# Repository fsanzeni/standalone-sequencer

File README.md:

# Standalone Super Sixteen Sequencer

This repository contains a hardware project built in KiCad—a reimagined and streamlined version of the [Super Sixteen project](https://github.com/matthewcieplak/super-sixteen). The goal is to create a standalone sequencer suitable for Eurorack and other synthesizer setups.

## Project Overview

The original Super Sixteen design has been reworked into a modular, three-board system:
- **7 Segment Display Board:** Manages visual output.
- **DAC and Mono Jack Board:** Provides digital-to-analog conversion and audio interfacing.
- **16-Step Keyboard Board:** Features 16 Cherry MX switches paired with reverse-mount RGB LEDs for step sequencing.

> All pins are broken out for flexible connectivity. The boards are designed to work together or independently based on your setup.

## Key Modifications

- **Simplified Design:** Removed the IO expander from the original Super Sixteen to reduce complexity.
- **Modular Approach:** Each board can function as part of a larger system or as a standalone unit.
- **Fabrication Update:** The PCBs are currently in fabrication. This project is a work in progress (WIP).

## Getting Started

1. **Hardware Designs:** Navigate to the appropriate subfolder in the `hardware` directory to access the KiCad schematic and PCB layout files. There are four subfolders in here: three correspond to the three PCBs (i.e., the "keyboard", the DAC and IO board, the 3-digit 7-segment display driver). The fourth folder contains the keyboard layout files I generated with the [Keyboard Layout Editor](https://www.keyboard-layout-editor.com/), which I imported into Kicad with the excellent [kicad-kbplacer](https://github.com/adamws/kicad-kbplacer) plugin. You can use the JSON file provided in this folder to variate the switches' layout without having to go through the hassle of moving things around precisely on Kicad :).
2. **Software Development:** The `software` folder is currently empty. Firmware or control software will be added as the project develops.
3. **Documentation:** Detailed build instructions, assembly guides, and design notes will be provided in the `documentation` folder over time.

## Hardware Design
As mentioned above, ths repo contains three PCBs:

_The keyboard PCB, with 16 steps and seven function buttons, all using Cherry MX keyswitches_

_The DAC, opamp and IO board. I am using DIP packages for the two main ICs just because I had them laying around. The conversion to SMD packages is trivial - and there's plenty of space on the board!_

_The 7 segment driver pcb. I'm using a three-digit unit, 0.56" tall. Everything is driven by a 74HC595 to reduce the pins needed for interfacing with a microcontroller._

You will notice the glaring omission of a microcontroller from this setup. I am using the venerable Arduino MEGA as the brains of the operation, so that I have enough pins not to worry about faffing around with multiplexers and the like. 

## Inspiration

This project draws inspiration from the original [Super Sixteen project](https://github.com/matthewcieplak/super-sixteen). Visit their repository to learn more about the design and evolution of the sequencer.

## License

Code: GPL3.0 Hardware: cc-by-sa-3.0

## Contributing

Contributions, issues, and feature requests are welcome. Please feel free to open an issue or submit a pull request.

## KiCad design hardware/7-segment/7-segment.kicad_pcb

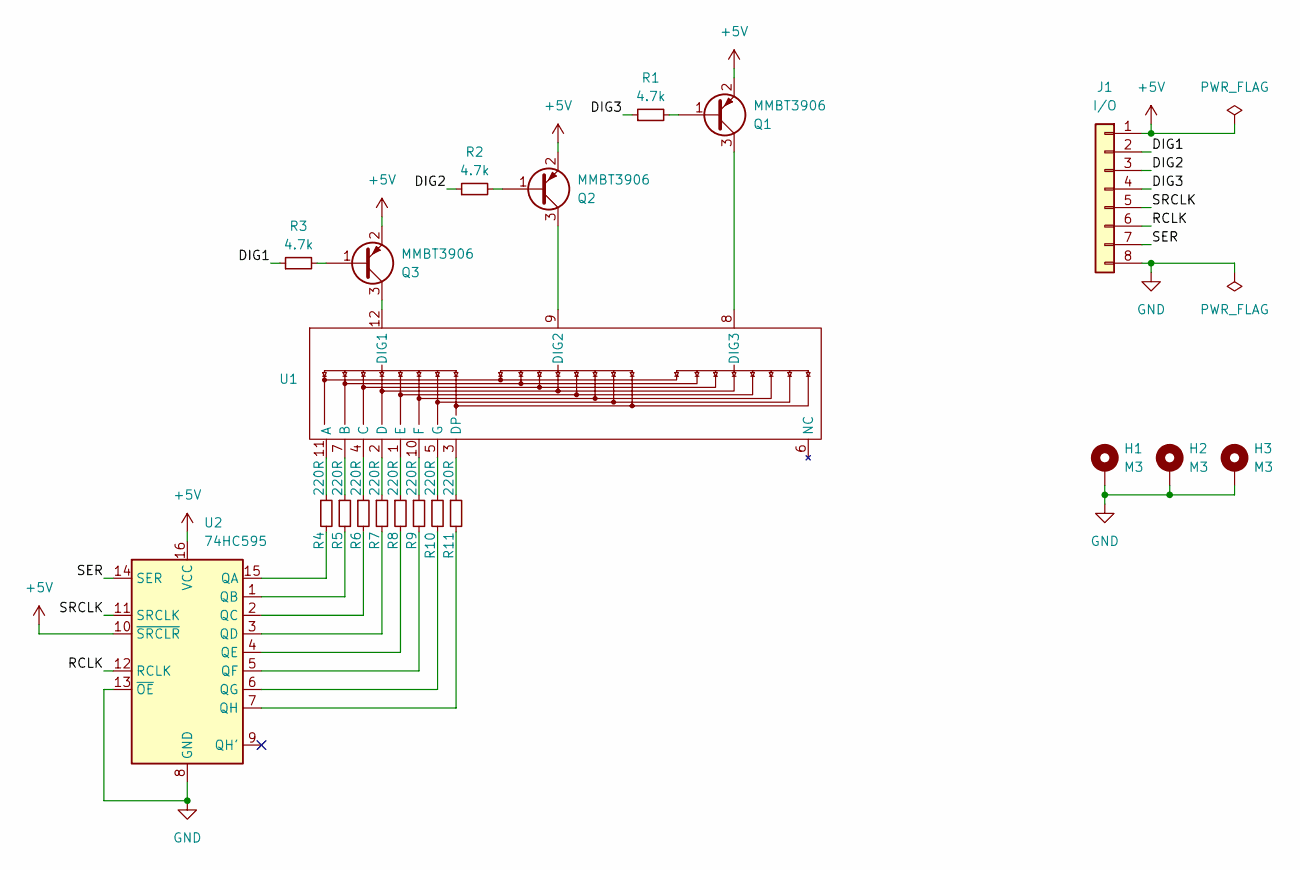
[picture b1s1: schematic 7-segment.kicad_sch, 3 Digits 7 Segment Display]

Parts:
H1, H2, H3: M3; MountingHole_3.2mm_M3_DIN965_Pad
J1: I/O; PinHeader_1x08_P2.54mm_Vertical
Q1, Q2, Q3: MMBT3906; SOT-23
R1, R2, R3: 4.7k; R_0603_1608Metric_Pad0.98x0.95mm_HandSolder
R4, R5, R6, R7, R8, R9, R10, R11: 220R; R_0603_1608Metric_Pad0.98x0.95mm_HandSolder
U1: FJ5361BH
U2: 74HC595; SOP-16_3.9x9.9mm_P1.27mm

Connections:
+5V: J1.1, Q1.2 (E), Q2.2 (E), Q3.2 (E), U2.10 (~SRCLR), U2.16 (VCC)
/DIG1: J1.2, R3.1
/DIG2: J1.3, R2.1
/DIG3: J1.4, R1.1
/RCLK: J1.6, U2.12 (RCLK)
/SER: J1.7, U2.14 (SER)
/SRCLK: J1.5, U2.11 (SRCLK)
GND: H1.1, H2.1, H3.1, J1.8, U2.8 (GND), U2.13 (~OE)
unnamed: Q1.1 (B), R1.2
unnamed: Q1.3 (C), U1.8 (DIG3)
unnamed: Q2.1 (B), R2.2
unnamed: Q2.3 (C), U1.9 (DIG2)
unnamed: Q3.1 (B), R3.2
unnamed: Q3.3 (C), U1.12 (DIG1)
unnamed: R4.1, U1.11 (A)
unnamed: R5.1, U1.7 (B)
unnamed: R6.1, U1.4 (C)
unnamed: R7.1, U1.2 (D)
unnamed: R11.1, U1.3 (DP)
unnamed: R8.1, U1.1 (E)
unnamed: R9.1, U1.10 (F)
unnamed: R10.1, U1.5 (G)
unnamed: R4.2, U2.15 (QA)
unnamed: R5.2, U2.1 (QB)
unnamed: R6.2, U2.2 (QC)
unnamed: R7.2, U2.3 (QD)
unnamed: R8.2, U2.4 (QE)
unnamed: R9.2, U2.5 (QF)
unnamed: R10.2, U2.6 (QG)
unnamed: R11.2, U2.7 (QH)

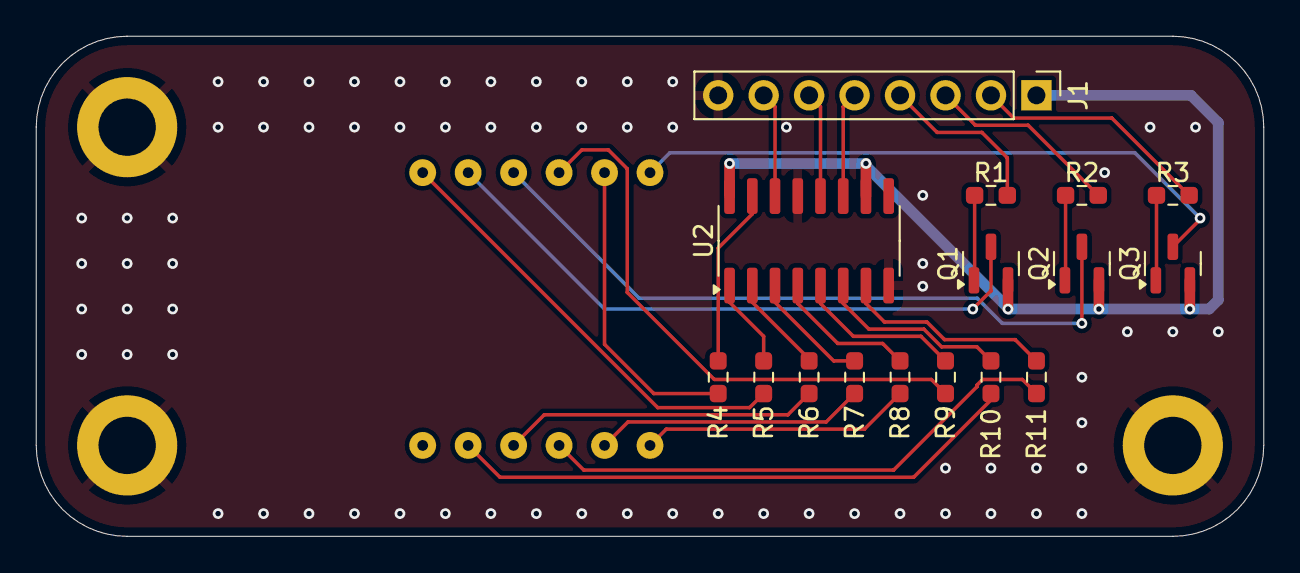
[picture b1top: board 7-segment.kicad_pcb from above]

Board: 2 copper layers, 68.6 x 27.9 mm, 20 parts (1 on the bottom side), 30 nets.

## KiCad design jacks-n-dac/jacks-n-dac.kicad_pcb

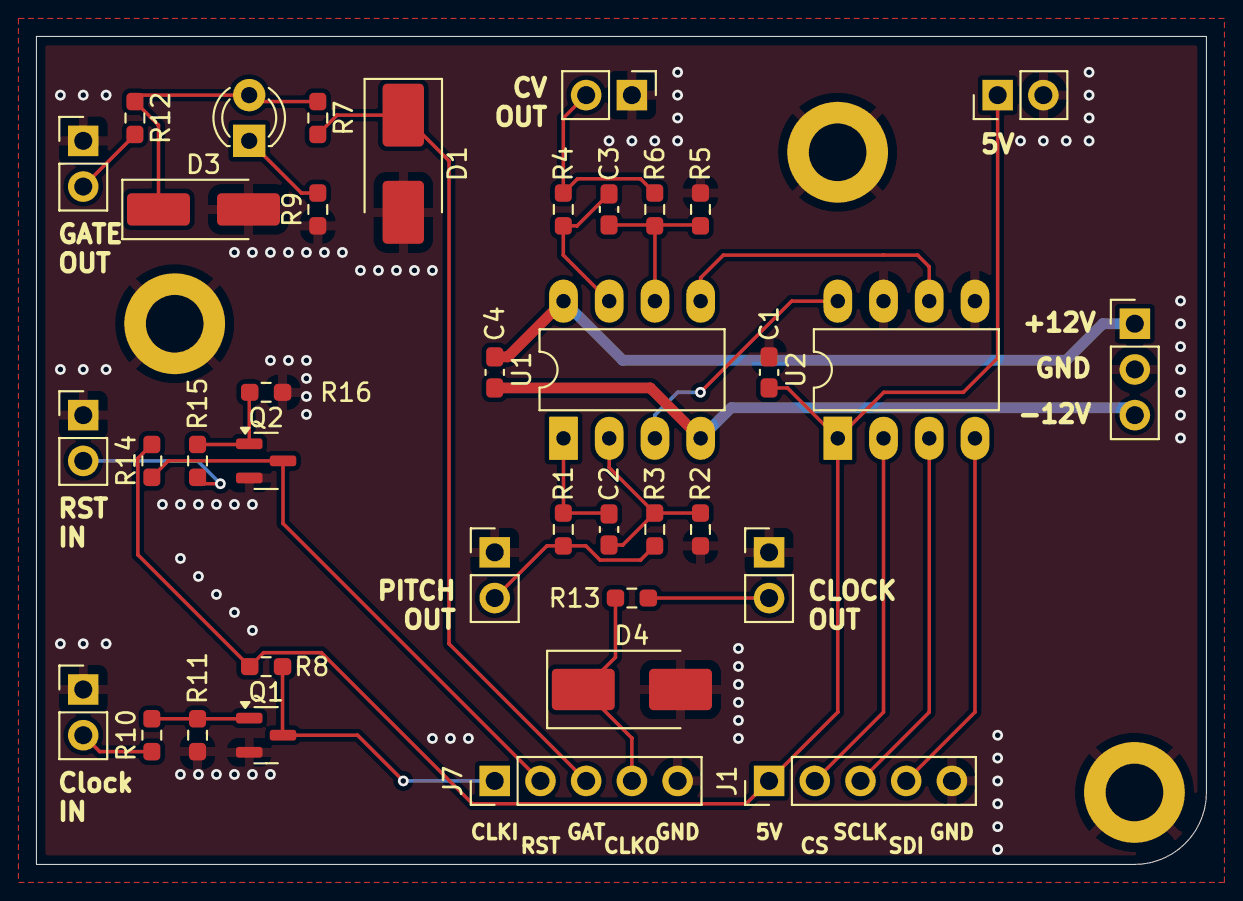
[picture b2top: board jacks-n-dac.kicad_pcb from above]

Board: 2 copper layers, 65.0 x 46.0 mm, 41 parts (0 on the bottom side), 27 nets.

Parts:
C1, C4: 100nF; C_0603_1608Metric_Pad1.08x0.95mm_HandSolder
C2, C3: 22pF; C_0603_1608Metric_Pad1.08x0.95mm_HandSolder
D1, D4: 1SMB5918BT3G; D_SMB_Handsoldering
D2: GATE; LED_D3.0mm_FlatTop
D3: SS34F; D_SMA_Handsoldering
H1, H2, H3: M3; MountingHole_3.2mm_M3_DIN965_Pad
J1: DAC; PinHeader_1x05_P2.54mm_Vertical
J2: 12V IN; PinHeader_1x03_P2.54mm_Vertical
J3: 5V IN; PinHeader_1x02_P2.54mm_Vertical
J4: GateOut; PinHeader_1x02_P2.54mm_Vertical
J5: ClockIn; PinHeader_1x02_P2.54mm_Vertical
J6: ClockOut; PinHeader_1x02_P2.54mm_Vertical
J7: INPUTS; PinHeader_1x05_P2.54mm_Vertical
J8: PitchOut; PinHeader_1x02_P2.54mm_Vertical
J9: CVOut; PinHeader_1x02_P2.54mm_Vertical
J10: ResetIn; PinHeader_1x02_P2.54mm_Vertical
Q1, Q2: MMBT3904; SOT-23
R1, R4, R7, R9, R12, R13: 1k; R_0603_1608Metric_Pad0.98x0.95mm_HandSolder
R2, R3, R5, R6, R8, R14: 10k; R_0603_1608Metric_Pad0.98x0.95mm_HandSolder
R10, R15: 100k; R_0603_1608Metric_Pad0.98x0.95mm_HandSolder
R11, R16: 1M; R_0603_1608Metric_Pad0.98x0.95mm_HandSolder
U1: TL072; DIP-8_W7.62mm_LongPads
U2: MCP4822; DIP-8_W7.62mm_LongPads

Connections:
+5V: C1.2, J1.1, J3.1, R8.2, R14.2, U2.1 (Vdd)
+12V: C4.2, J2.1, U1.8 (V+)
-12V: C4.1, J2.3, U1.4 (V-)
/CLKIN: J7.1, Q1.3 (C), R8.1
/CLKOUT: D4.1 (K), J7.4, R13.2
/CS_DAC: J1.2, U2.2 (~CS)
/CV: J9.2, R4.2, R6.2
/GATE: D1.1 (K), J7.3, R7.2
/MOSI: J1.4, U2.4 (SDI)
/PITCH: J8.2, R1.2, R3.2
/RSTIN: J7.2, Q2.3 (C), R14.1
/SCLK: J1.3, U2.3 (SCK)
GND: C1.1, D1.2 (A), D3.2 (A), D4.2 (A), H1.1, H2.1, H3.1, J1.5, J2.2, J3.2, J4.1, J5.1, J6.1, J7.5, J8.1, J9.1, J10.1, Q1.2 (E), Q2.2 (E), R2.1, R5.1, R9.1, R11.1, R16.1, U2.5 (~LDAC), U2.7 (Vss)
unnamed: C2.2, R1.1, U1.1
unnamed: C3.2, R4.1, U1.7
unnamed: D2.2 (A), D3.1 (K), R7.1, R12.1
unnamed: D2.1 (K), R9.2
unnamed: J4.2, R12.2
unnamed: J5.2, R10.1
unnamed: J6.2, R13.1
unnamed: J10.2, R15.1
unnamed: Q1.1 (B), R10.2, R11.2
unnamed: Q2.1 (B), R15.2, R16.2
unnamed: U1.3 (+), U2.8 (VA)
unnamed: C2.1, R2.2, R3.1, U1.2 (-)
unnamed: U1.5 (+), U2.6 (VB)
unnamed: C3.1, R5.2, R6.1, U1.6 (-)

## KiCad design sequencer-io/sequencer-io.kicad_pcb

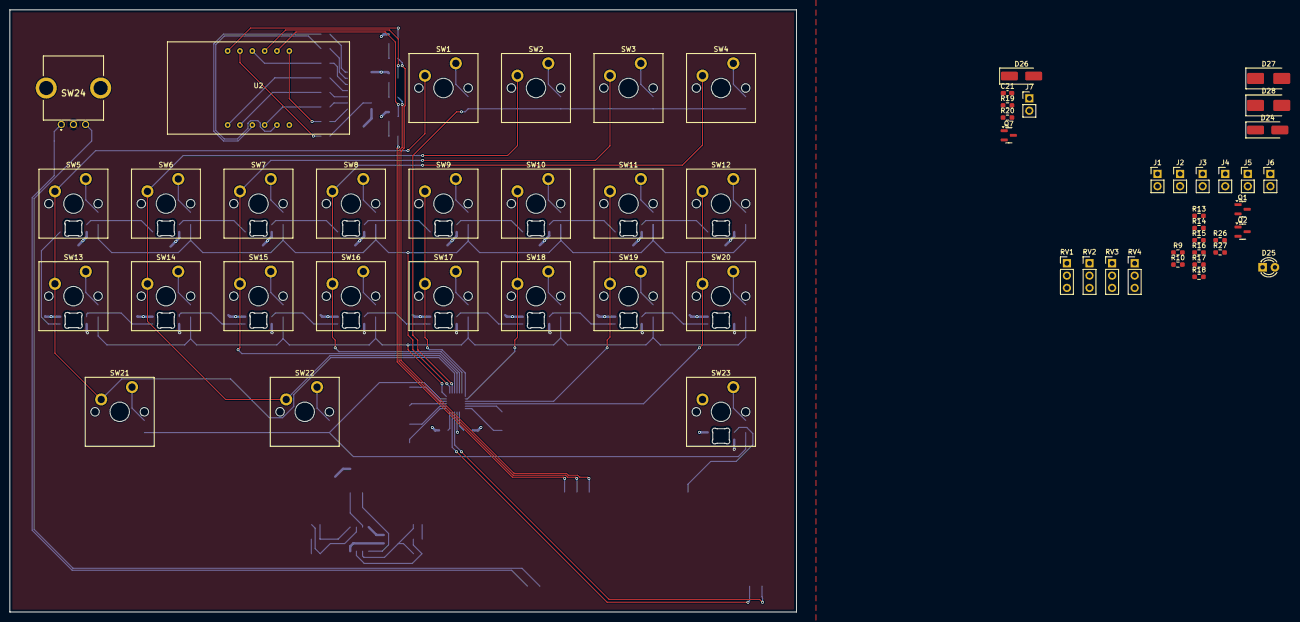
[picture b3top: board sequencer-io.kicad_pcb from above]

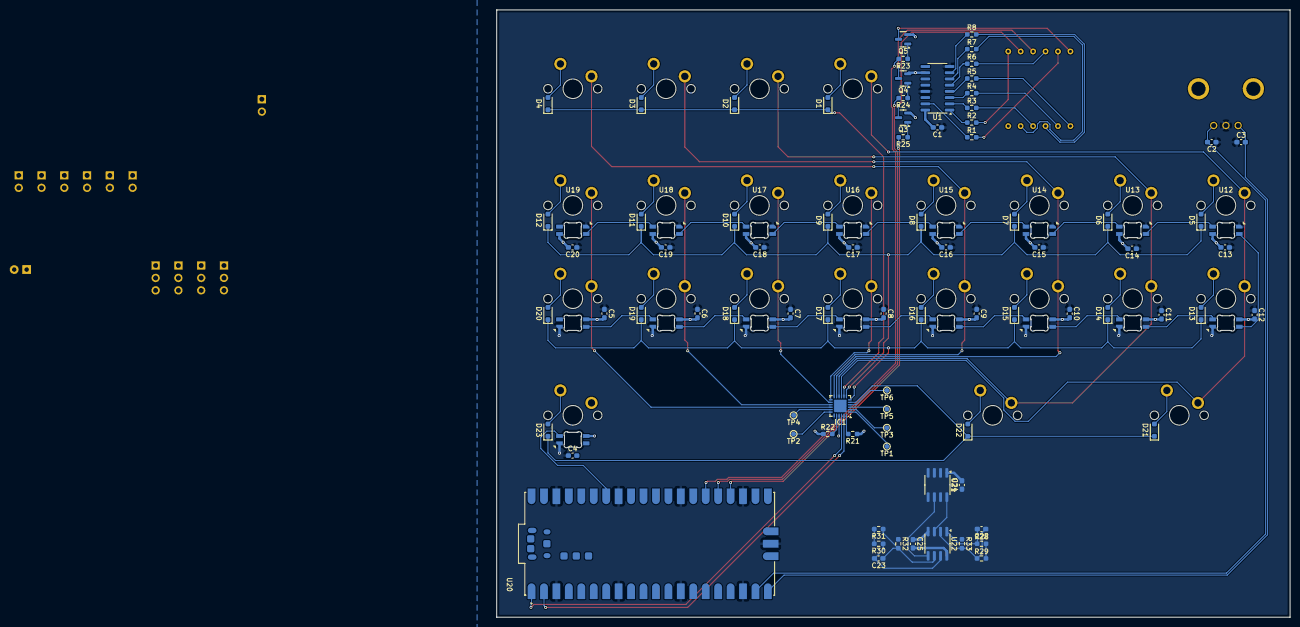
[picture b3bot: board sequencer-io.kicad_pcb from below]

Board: 4 copper layers, 162.0 x 124.0 mm, 154 parts (97 on the bottom side), 113 nets.

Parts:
C1, C2, C3, C4, C5, C6, C7, C8, C9, C10, C11, C12, C13, C14, C15, C16, C17, C18, C19, C20, C24, C25: 100nF; C_0603_1608Metric_Pad1.08x0.95mm_HandSolder
C21: 47uF; C_0603_1608Metric_Pad1.08x0.95mm_HandSolder
C22, C23: 22pF; C_0603_1608Metric_Pad1.08x0.95mm_HandSolder
D1, D2, D3, D4, D5, D6, D7, D8, D9, D10, D11, D12, D13, D14, D15, D16, D17, D18, D19, D20, D21, D22, D23: 1N4148W; D_SOD-323_HandSoldering
D24, D26: SS34F; D_SMA_Handsoldering
D25: GATE; LED_D3.0mm_FlatTop
D27, D28: 1SMB5918BT3G; D_SMB_Handsoldering
IC1: TCA8418RTWR; QFN-24-1EP_4x4mm_P0.5mm_EP2.5x2.5mm
J1: ClockIn; PinHeader_1x02_P2.54mm_Vertical
J2: GateOut; PinHeader_1x02_P2.54mm_Vertical
J3: ClockOut; PinHeader_1x02_P2.54mm_Vertical
J4: PitchOut; PinHeader_1x02_P2.54mm_Vertical
J5: CVOut; PinHeader_1x02_P2.54mm_Vertical
J6: ResetIn; PinHeader_1x02_P2.54mm_Vertical
J7: 5V EXT; PinHeader_1x02_P2.54mm_Vertical
Q1, Q2: MMBT3904; SOT-23
Q3, Q4, Q5: MMBT3906; SOT-23
Q7: DMG2305UX-7; SOT-23
R1, R2, R3, R4, R5, R6, R7, R8: 100R; R_0603_1608Metric_Pad0.98x0.95mm_HandSolder
R9, R16, R19, R20, R21, R22, R29, R31, R32, R33: 10k; R_0603_1608Metric_Pad0.98x0.95mm_HandSolder
R10, R15, R26, R27, R28, R30: 1k; R_0603_1608Metric_Pad0.98x0.95mm_HandSolder
R13, R17: 100k; R_0603_1608Metric_Pad0.98x0.95mm_HandSolder
R14, R18: 1M; R_0603_1608Metric_Pad0.98x0.95mm_HandSolder
R23, R24, R25: 680R; R_0603_1608Metric_Pad0.98x0.95mm_HandSolder
RV1: PITCH; PinHeader_1x03_P2.54mm_Vertical
RV2: OCTAVE; PinHeader_1x03_P2.54mm_Vertical
RV3: LENGTH; PinHeader_1x03_P2.54mm_Vertical
RV4: CV; PinHeader_1x03_P2.54mm_Vertical
SW1, SW2, SW3, SW4, SW5, SW6, SW7, SW8, SW9, SW10, SW11, SW12, SW13, SW14, SW15, SW16, SW17, SW18, SW19, SW20, SW23: SW_Push; SW_Cherry_MX_PCB_1.00u
SW21, SW22: SW_Push; SW_Cherry_MX_PCB_2.00u
SW24: RotaryEncoder; EC12E2430404
TP1, TP2, TP3, TP4, TP5, TP6: TestPoint_Small; TestPoint_Pad_D1.0mm
U1: 74HC595; SOIC-16_3.9x9.9mm_P1.27mm
U2: FJ5361BH
U3, U4, U5, U6, U7, U8, U9, U10, U11: SK6812MINI-E-012
U12, U13, U14, U15, U16, U17, U18, U19: SK6812MINI-E-012-ROT
U20: SC0915
U21: MCP4822; SOIC-8_3.9x4.9mm_P1.27mm
U22: TL072; SOIC-8_3.9x4.9mm_P1.27mm

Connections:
+3.3V: IC1.21 (VCC), R9.2, R16.2, R19.1, R20.1, R21.1, R22.1, RV1.1, RV2.1, RV3.1, RV4.1
+5V: C1.2, C4.2, C5.2, C6.2, C7.2, C8.2, C9.2, C10.2, C11.2, C12.2, C13.2, C14.2, C15.2, C16.2, C17.2, C18.2, C19.2, C20.2, C21.2, C24.2, D26.1 (K), Q3.2 (E), Q4.2 (E), Q5.2 (E), Q7.2 (S), U1.10 (~SRCLR), U1.16 (VCC), U3.3 (VDD), U4.3 (VDD), U5.3 (VDD), U6.3 (VDD), U7.3 (VDD), U8.3 (VDD), U9.3 (VDD), U10.3 (VDD), U11.3 (VDD), U12.3 (VDD), U13.3 (VDD), U14.3 (VDD), U15.3 (VDD), U16.3 (VDD), U17.3 (VDD), U18.3 (VDD), U19.3 (VDD), U20.39 (VSYS), U21.1 (Vdd)
+12V: C25.2, U22.8 (V+)
-12V: C25.1, U22.4 (V-)
/DAC/CV: R30.2, R31.2
/DAC/PITCH: R28.2, R29.2
/DAC/SCLK: U1.11 (SRCLK), U21.3 (SCK)
/IOs/CLKIN: Q1.3 (C), R9.1
/IOs/CLKOUT: D28.1 (K), R27.2
/IOs/DIGIT_1: R23.2, U20.26 (GP20)
/IOs/DIGIT_2: R24.2, U20.25 (GP19)
/IOs/DIGIT_3: R25.2, U20.24 (GP18)
/IOs/ENC_A: C3.2, SW24.A, U20.20 (GP15)
/IOs/ENC_B: C2.2, SW24.B, U20.19 (GP14)
/IOs/GATE: D27.1 (K), R26.2
/IOs/RSTIN: Q2.3 (C), R16.1
/LEDs/PXL: U3.2 (DIN), U20.34 (GP28)
/Switches/SCL: IC1.23 (SCL), R20.2, U20.2 (GP1)
/Switches/SDA: IC1.22 (SDA), R19.2, U20.1 (GP0)
COL0: IC1.9 (COL0), SW1.1, SW5.1, SW13.1, SW21.1
COL1: IC1.10 (COL1), SW2.1, SW6.1, SW14.1, SW22.1
COL2: IC1.11 (COL2), SW3.1, SW7.1, SW15.1, SW23.1
COL3: IC1.12 (COL3), SW4.1, SW8.1, SW16.1
COL4: IC1.13 (COL4), SW9.1, SW17.1
COL5: IC1.14 (COL5), SW10.1, SW18.1
COL6: IC1.15 (COL6), SW11.1, SW19.1
COL7: IC1.16 (COL7), SW12.1, SW20.1
GND: C1.1, C2.1, C3.1, C4.1, C5.1, C6.1, C7.1, C8.1, C9.1, C10.1, C11.1, C12.1, C13.1, C14.1, C15.1, C16.1, C17.1, C18.1, C19.1, C20.1, C21.1, C24.1, D24.2 (A), D27.2 (A), D28.2 (A), IC1.19 (GND), IC1.25 (EP), J7.2, Q1.2 (E), Q2.2 (E), R10.1, R14.1, R18.1, R32.1, R33.1, RV4.3, SW24.C, U1.8 (GND), U1.13 (~OE), U3.1 (GND), U4.1 (GND), U5.1 (GND), U6.1 (GND), U7.1 (GND), U8.1 (GND), U9.1 (GND), U10.1 (GND), U11.1 (GND), U12.1 (GND), U13.1 (GND), U14.1 (GND), U15.1 (GND), U16.1 (GND), U17.1 (GND), U18.1 (GND), U19.1 (GND), U20.3 (GND), U20.8 (GND), U20.13 (GND), U20.18 (GND), U20.23 (GND), U20.28 (GND), U20.33 (AGND), U20.38 (GND), U20.D2 (GND), U21.5 (~LDAC), U21.7 (Vss)
unnamed: C22.2, R28.1, U22.1
unnamed: C23.2, R30.1, U22.7
unnamed: D1.2 (A), SW1.2
unnamed: D2.2 (A), SW2.2
unnamed: D3.2 (A), SW3.2
unnamed: D4.2 (A), SW4.2
unnamed: D5.2 (A), SW5.2
unnamed: D6.2 (A), SW6.2
unnamed: D7.2 (A), SW7.2
unnamed: D8.2 (A), SW8.2
unnamed: D9.2 (A), SW9.2
unnamed: D10.2 (A), SW10.2
unnamed: D11.2 (A), SW11.2
unnamed: D12.2 (A), SW12.2
unnamed: D13.2 (A), SW13.2
unnamed: D14.2 (A), SW14.2
unnamed: D15.2 (A), SW15.2
unnamed: D16.2 (A), SW16.2
unnamed: D17.2 (A), SW17.2
unnamed: D18.2 (A), SW18.2
unnamed: D19.2 (A), SW19.2
unnamed: D20.2 (A), SW20.2
unnamed: D21.2 (A), SW21.2
unnamed: D22.2 (A), SW22.2
unnamed: D23.2 (A), SW23.2
unnamed: D24.1 (K), D25.2 (A), R15.1, R26.1
unnamed: D25.1 (K), R10.2
unnamed: D26.2 (A), Q7.1 (G), U20.40 (VBUS)
unnamed: IC1.17 (COL8), TP4.1
unnamed: IC1.18 (COL9), TP2.1
unnamed: IC1.4 (ROW4), TP6.1
unnamed: IC1.3 (ROW5), TP5.1
unnamed: IC1.2 (ROW6), TP3.1
unnamed: IC1.1 (ROW7), TP1.1
unnamed: IC1.24 (~INT), R21.2
unnamed: IC1.20 (~RESET), R22.2
unnamed: J7.1, Q7.3 (D)
unnamed: Q1.1 (B), R13.2, R14.2
unnamed: Q2.1 (B), R17.2, R18.2
unnamed: Q3.1 (B), R25.1
unnamed: Q3.3 (C), U2.8 (DIGIT_3)
unnamed: Q4.1 (B), R24.1
unnamed: Q4.3 (C), U2.9 (DIGIT_2)
unnamed: Q5.1 (B), R23.1
unnamed: Q5.3 (C), U2.12 (DIGIT_1)
unnamed: R1.1, U1.15 (QA)
unnamed: R2.1, U1.1 (QB)
unnamed: R3.1, U1.2 (QC)
unnamed: R4.1, U1.3 (QD)
unnamed: R5.1, U1.4 (QE)
unnamed: R6.1, U1.5 (QF)
unnamed: R7.1, U1.6 (QG)
unnamed: R8.1, U1.7 (QH)
unnamed: R1.2, U2.11 (A)
unnamed: R2.2, U2.7 (B)
unnamed: R3.2, U2.4 (C)
unnamed: R4.2, U2.2 (D)
unnamed: R8.2, U2.3 (DP)
unnamed: R5.2, U2.1 (E)
unnamed: R6.2, U2.10 (F)
unnamed: R7.2, U2.5 (G)
unnamed: U3.4 (DOUT), U4.2 (DIN)
unnamed: U4.4 (DOUT), U5.2 (DIN)
unnamed: U5.4 (DOUT), U6.2 (DIN)
unnamed: U6.4 (DOUT), U7.2 (DIN)
unnamed: U7.4 (DOUT), U8.2 (DIN)
unnamed: U8.4 (DOUT), U9.2 (DIN)
unnamed: U9.4 (DOUT), U10.2 (DIN)
unnamed: U10.4 (DOUT), U11.2 (DIN)
unnamed: U11.4 (DOUT), U12.2 (DIN)
unnamed: U12.4 (DOUT), U13.2 (DIN)
unnamed: U13.4 (DOUT), U14.2 (DIN)
unnamed: U14.4 (DOUT), U15.2 (DIN)
unnamed: U15.4 (DOUT), U16.2 (DIN)
unnamed: U16.4 (DOUT), U17.2 (DIN)
unnamed: U17.4 (DOUT), U18.2 (DIN)
unnamed: U18.4 (DOUT), U19.2 (DIN)
unnamed: U21.8 (VA), U22.3 (+)
unnamed: U21.6 (VB), U22.5 (+)
unnamed: C22.1, R29.1, R33.2, U22.2 (-)
unnamed: C23.1, R31.1, R32.2, U22.6 (-)
ROW0: D1.1 (K), D2.1 (K), D3.1 (K), D4.1 (K), IC1.8 (ROW0)
ROW1: D5.1 (K), D6.1 (K), D7.1 (K), D8.1 (K), D9.1 (K), D10.1 (K), D11.1 (K), D12.1 (K), IC1.7 (ROW1)
ROW2: D13.1 (K), D14.1 (K), D15.1 (K), D16.1 (K), D17.1 (K), D18.1 (K), D19.1 (K), D20.1 (K), IC1.6 (ROW2)
ROW3: D21.1 (K), D22.1 (K), D23.1 (K), IC1.5 (ROW3)

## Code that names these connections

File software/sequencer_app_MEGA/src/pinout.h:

#pragma once

// MISC PINS
#define GATE_PIN                9
//#define LDAC_PIN 1
#define CLOCK_OUT_PIN           53
#define CLOCK_IN_PIN            52
#define RESET_PIN               10

// KEYBOARD PINS
#define ROW0_PIN                38
#define ROW1_PIN                40
#define ROW2_PIN                42
#define ROW3_PIN                44

#define COL0_PIN                31
#define COL1_PIN                33
#define COL2_PIN                35
#define COL3_PIN                37
#define COL4_PIN                39
#define COL5_PIN                41
#define COL6_PIN                43
#define COL7_PIN                45

const int buttonRows[4] = { ROW0_PIN, ROW1_PIN, ROW2_PIN, ROW3_PIN };
const int buttonCols[8] = { COL0_PIN, COL1_PIN, COL2_PIN, COL3_PIN,
                            COL4_PIN, COL5_PIN, COL6_PIN, COL7_PIN };

// LED PINS
#define GLIDE_NEOPIXEL_PIN      23
#define LED_MATRIX_PIN          2

// TODO
// #define GLIDE_LED_PIN 15 //these 8 are on the button driver chip, not the MCU
#define GLIDE_PIN               14
#define REPEAT_PIN              13
#define RECORD_PIN              12
#define SAVE_PIN                11 
#define LOAD_PIN                10 
#define PLAY_PIN                9 
#define SHIFT_PIN               8

// TODO - CHIP SELECT PINS
// #define CS0_PIN  10 //MCP23S17 for buttons, aux LEDS
// #define CS1_PIN  9  //Display/matrix shift registers
#define CSFLASH_PIN             4  //Flash memory


// DIGIT DISPLAY PINS
#define DIGIT_1_PIN             16
#define DIGIT_2_PIN             17
#define DIGIT_3_PIN             18
#define DIO_PIN                 21
#define RCLK_PIN                20
#define SCLK_PIN                19

// DAC PINS
#define CSDAC_PIN               7
#define DAC_DATA_PIN            5
#define DAC_CLOCK_PIN           6

// POTENTIOMETER PINS - TODO
#define ANALOG_PIN_1            A0
#define ANALOG_PIN_2            A1
#define ANALOG_PIN_3            A2
#define ANALOG_PIN_4            A3

// ENCODER PINS
#define ENC_A_PIN               A4
#define ENC_B_PIN               A5
#define ENC_PORT                PINC

// GAIN
#define GAIN_1                  0x1
#define GAIN_2                  0x0

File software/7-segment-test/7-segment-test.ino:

// Arduino pin assignments for 74HC595
const int dataPin = 21;   // SER (pin 14) of 74HC595
const int clockPin = 19;  // SRCLK (pin 11) of 74HC595
const int latchPin = 20;  // RCLK (pin 12) of 74HC595

// Digit control pins (active low for common anode via mmbt3906)
// DIGIT1: pin 7, DIGIT2: pin 5, DIGIT3: pin 3
const int digitPins[3] = {7, 5, 3};

// Common anode segment codes for digits 0-9
// (These values are the bitwise inversions of the typical common cathode codes)
// Bit order: bit0 = A, bit1 = B, bit2 = C, bit3 = D, bit4 = E, bit5 = F, bit6 = G, bit7 = DP (unused)
byte digitCodes[10] = {
  0xC0, // 0: inverted 0x3F (segments A, B, C, D, E, F on)
  0xF9, // 1: inverted 0x06 (segments B, C on)
  0xA4, // 2: inverted 0x5B (segments A, B, D, E, G on)
  0xB0, // 3: inverted 0x4F (segments A, B, C, D, G on)
  0x99, // 4: inverted 0x66 (segments B, C, F, G on)
  0x92, // 5: inverted 0x6D (segments A, C, D, F, G on)
  0x82, // 6: inverted 0x7D (segments A, C, D, E, F, G on)
  0xF8, // 7: inverted 0x07 (segments A, B, C on)
  0x80, // 8: inverted 0x7F (all segments on)
  0x90  // 9: inverted 0x6F (segments A, B, C, D, F, G on)
};

unsigned long previousMillis = 0;
const unsigned long interval = 1000; // Update the count every 1 second
int count = 0;

void setup() {
  // Initialize digit control pins
  for (int i = 0; i < 3; i++) {
    pinMode(digitPins[i], OUTPUT);
    digitalWrite(digitPins[i], HIGH); // Turn off all digits (active low)
  }
  
  // Initialize 74HC595 control pins
  pinMode(dataPin, OUTPUT);
  pinMode(clockPin, OUTPUT);
  pinMode(latchPin, OUTPUT);
  
  // Clear the shift register (all segments off: 0xFF means no LED lit)
  digitalWrite(latchPin, LOW);
  shiftOut(dataPin, clockPin, MSBFIRST, 0xFF);
  digitalWrite(latchPin, HIGH);
}

void loop() {
  // Update the count every 1 second
  unsigned long currentMillis = millis();
  if (currentMillis - previousMillis >= interval) {
    previousMillis = currentMillis;
    count++;
    if(count >= 1000) {
      count = 0; // Roll over after 999
    }
  }
  
  // Extract hundreds, tens, and ones
  int hundreds = count / 100;
  int tens = (count / 10) % 10;
  int ones = count % 10;
  
  // Refresh each digit one at a time (multiplexing)
  displayDigit(0, hundreds); // Left digit (hundreds)
  displayDigit(1, tens);     // Middle digit (tens)
  displayDigit(2, ones);     // Right digit (ones)
}

// This function displays a single digit on one of the three displays
// digitIndex: 0 for hundreds, 1 for tens, 2 for ones
// number: value between 0 and 9 to display
void displayDigit(int digitIndex, int number) {
  // Turn off all digits
  for (int i = 0; i < 3; i++) {
    digitalWrite(digitPins[i], HIGH);
  }
  
  // Send the segment data for the given number to the 74HC595
  byte segData = digitCodes[number];
  digitalWrite(latchPin, LOW);
  shiftOut(dataPin, clockPin, MSBFIRST, segData);
  digitalWrite(latchPin, HIGH);
  
  // Enable the selected digit (active low)
  digitalWrite(digitPins[digitIndex], LOW);
  delay(2); // Briefly display this digit (adjust delay as needed)
  digitalWrite(digitPins[digitIndex], HIGH); // Turn it off before next refresh
}

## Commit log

2025-02-10 Edited PCB
2025-02-10 Added TCA8418
2025-02-11 Cleaned up schematic, added DAC and outputs
2025-02-11 Added gitignore
2025-02-11 lil update
2025-02-11 edits
2025-02-19 removed rp2040
2025-02-25 complete overhaul
2025-02-28 tidy up - remove duplicates
2025-02-28 tidy up
2025-03-07 clean up, added pdf schematics
2025-03-09 added test sketch for 7 segment
2025-03-14 added ino sketch to test keypad
2025-03-17 added sketch
2025-03-25 display code porting
2025-03-25 display porting finished
2025-03-28 ported buttons.cpp and .h
2025-03-28 updated firmware - untested
2025-03-29 fixed font and character displaying function
2025-03-30 corrected resistor values
2025-03-30 fixed display init function
2025-03-30 corrected pin assignments
2025-03-30 fixed setDisplayAlpha()
2025-03-30 test
2025-03-31 formatting
2025-04-02 fixes
